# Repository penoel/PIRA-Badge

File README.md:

# PIRA-Badge
A badge for the 2018 summer AAPT conference.  It consist of the PIRA logo with a string of leds along a lightning bolt that randomly flash.  It is controlled through an attiny85 and powered by a coin cell.

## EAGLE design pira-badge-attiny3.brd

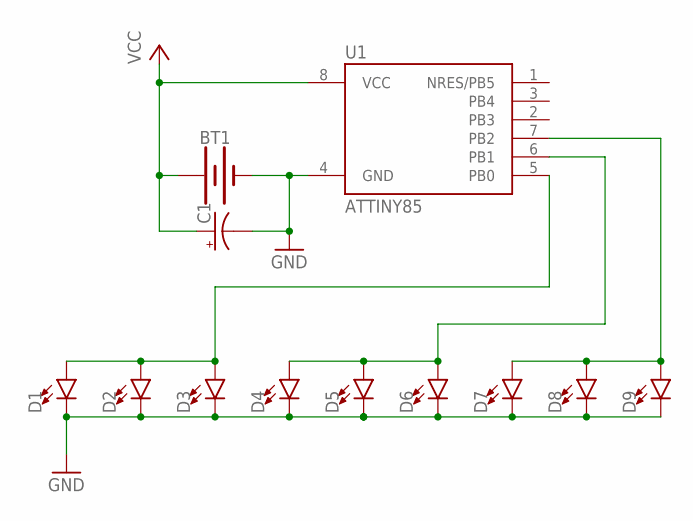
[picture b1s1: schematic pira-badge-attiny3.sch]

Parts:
BT1: BATTERY-24.5MM_PTH; BATTCON_24.5MM_PTH
C1: CPOL-USCT3216; CT3216
D1, D2, D3, D4, D5, D6, D7, D8, D9: LED1206; LED-1206
U1: ATTINY85; SOIC8_EIAJ_208MIL

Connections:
GND: BT1.2 (-), C1.-, D1.C, D2.C, D3.C, D4.C, D5.C, D6.C, D7.C, D8.C, D9.C, U1.4 (GND)
unnamed: D7.A, D8.A, D9.A, U1.7 (PB2)
unnamed: D1.A, D2.A, D3.A, U1.5 (PB0)
unnamed: D4.A, D5.A, D6.A, U1.6 (PB1)
VCC: BT1.3 (+), C1.+, U1.8 (VCC)

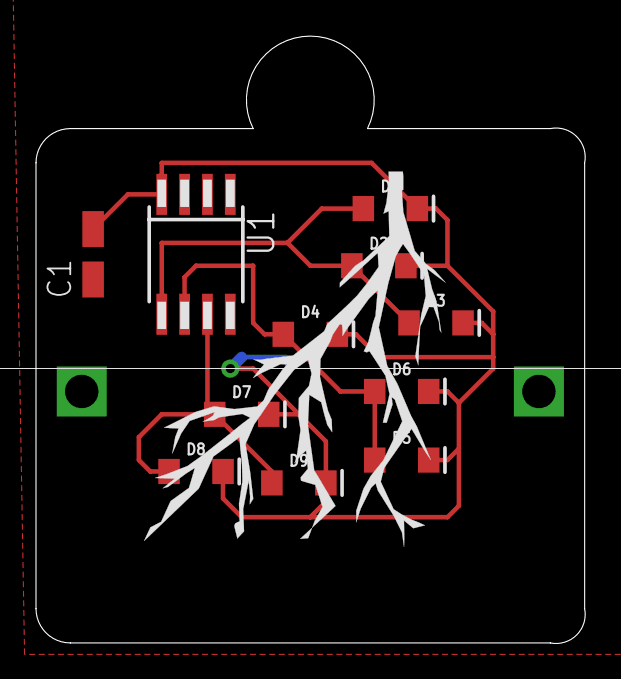
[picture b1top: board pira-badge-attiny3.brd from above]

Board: 2 copper layers, 30.5 x 33.7 mm, 12 parts (1 on the bottom side), 5 nets.

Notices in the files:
parts and their libraries:
SparkFun-Batteries: Licensing: Creative Commons ShareAlike 4.0 International - https://creativecommons.org/licenses/by-sa/4.0
